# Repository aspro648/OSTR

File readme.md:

Open Source Turtle Robot (OSTR)
-------------------------------

I designed this project for a 10-hour workshop for [ChickTech.org](http://www.chicktech.org) whose goal is to introduce teenage women to STEM topics. The goals for this project were:

- Easy to build.
- Easy to program.
- Did something interesting.
- Low-cost so participants could take it home and continue to learn.

Robotics is the exciting intersection of a number of engineering fields including mechanical engineering, electrical engineering, and computer science. This project was designed to make learning about these fields accessible and exciting.

Turtle robots are controled by simple instructions like "forward(distance)" and "left(degrees)", and their visual tracks are instructive as well as entertaining. They also demonstrate how systems with simple rules can have complex behaviors, something we see in nature all the time.

New to Version 2 is the shift from the Adafruit [Trinket Pro](https://www.adafruit.com/product/2010) to their [ItsyBitsy 32U4 3V](https://www.adafruit.com/product/3675) which enables USB communication for easier troubleshooting, or the [ItsyBitsy M0 Express](https://www.adafruit.com/product/3727) which allows programing in Python!

Python is a popular and easy to learn programming language that already has Turle Graphics built in.  Since the robots instructions are the same, programs and paterns can be evaluated on the computer and then run on the robot. 
```python
from turtle import *

for x in range(5):
    forward(100)
    right(144)
```

Here is a great Hour of Code tutorial to get you introduced to Python Turtle: [https://groklearning.com/hoc/activity/snowflake/](https://groklearning.com/hoc/activity/snowflake/).  The only thing pysical Turtle Robot can't do is change colors automatically, but you can alway swap the pens around manually.

### Video of Turtle Robot (V1) in action:

This robot has been refined through a number workshops, but still has room for improvement.  Please share your ideas and modifications so it can continue to improve.

Bill Of Materials
-----------------
In bulk quantities, the cost per robot is about $40.  The Bill of Materials is available [here](/V2/BOM.md).
Having told you the at-cost and provided you my BOM, I'd still offer to [sell you a kit](https://www.tindie.com/products/MakersBox/open-source-turtle-robot-ostr/) if you'd like to pay for the convenience of a single-source or you don't have access to a 3D printer.  This also allows me continue development for future workshops.

Design Files
------------
The electronics were designed using Open Source [KiCad](http://kicad.org/). Design files are located in the [design_files](V2/design_files/) folder.  You can oogle the [schematic](V2/docs/Schematic.pdf).

The 3D Design files were created with a combination of [FreeCad](https://www.freecadweb.org/), [OpenSCAD](https://www.openscad.org/) (both Open Source), and online [TinkerCad](https://www.tinkercad.com/).  Design files and STLs are located in the [3D](V2/3D/) folder.

Firmware
--------
This project is programed using Open Source [Arduino](https://www.arduino.cc/) or Adafruit's [Circuit Python](https://learn.adafruit.com/welcome-to-circuitpython/what-is-circuitpython) depending on the microcontroller used. The firmware is located in the [firmware](V2/firmware/) folder.  Instructions for setting up the Arduino environment for the ItsyBitsy 32U4 are at [https://learn.adafruit.com/introducting-itsy-bitsy-32u4/](https://learn.adafruit.com/introducting-itsy-bitsy-32u4/).

Assembly Instructions
---------------------
[https://www.instructables.com/id/OSTR/](https://www.instructables.com/id/OSTR/).  
Also, check the [docs](V2/docs/) folder for handouts, etc.  May still have pictures of V1 assembly, but they are nearly identical.

License
-------
[Attribution-ShareAlike 3.0 United States (CC BY-SA 3.0 US)](https://creativecommons.org/licenses/by-sa/3.0/us/)

You are free to:

- Share — copy and redistribute the material in any medium or format
- Adapt — remix, transform, and build upon the material

Under the following terms:

- Attribution — You must give appropriate credit, provide a link to the license, and indicate if changes were made. You may do so in any reasonable manner, but not in any way that suggests the licensor endorses you or your use.
- ShareAlike — If you remix, transform, or build upon the material, you must distribute your contributions under the same license as the original.

Certified Open Source:
----------------------
This project as been certified by the [Open Source Hardward Association](https://certification.oshwa.org/):

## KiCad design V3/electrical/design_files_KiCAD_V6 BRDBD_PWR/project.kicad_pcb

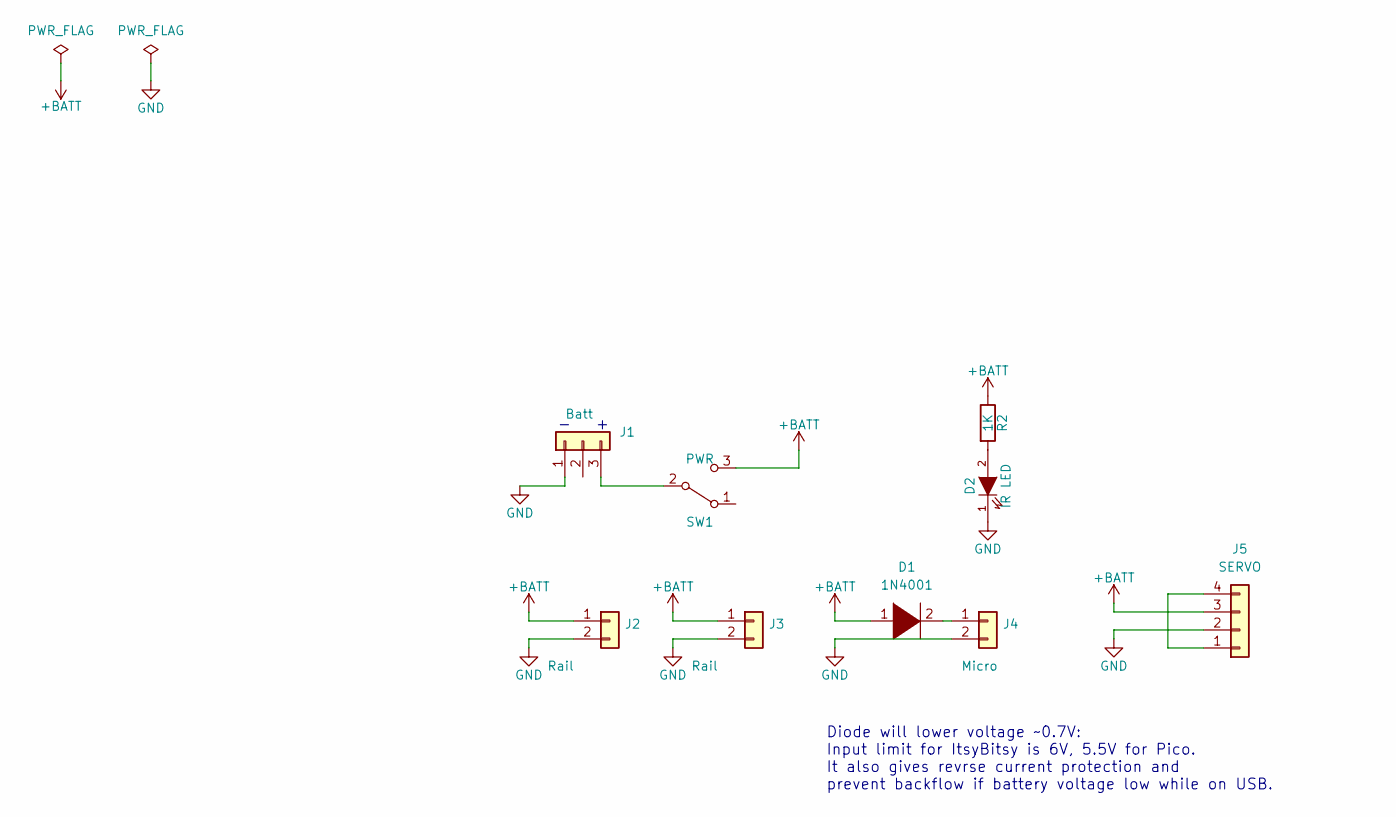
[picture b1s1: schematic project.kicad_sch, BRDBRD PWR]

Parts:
D1: 1N4001; D_DO-34_SOD68_P7.62mm_Horizontal
D2: IR LED; LED_D3.0mm
J1: Batt; TerminalBlock_Phoenix_PT-1,5-3-3.5-H_1x03_P3.50mm_Horizontal
J2, J3: Rail; PinHeader_1x02_P2.54mm_Vertical
J4: Micro; PinHeader_1x02_P2.54mm_Vertical
J5: SERVO; PinHeader_1x04_P2.54mm_Vertical
R2: 1K; Resistor_Horz
SW1: PWR; SW_Micro_SPST

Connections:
+BATT: D1.1 (K), J2.1, J3.1, J5.3, R2.1, SW1.3 (C)
GND: D2.1 (K), J1.1, J2.2, J3.2, J4.2, J5.2
unnamed: D2.2 (A), R2.2
unnamed: J1.3, SW1.2 (B)
unnamed: D1.2 (A), J4.1
unnamed: J5.1, J5.4

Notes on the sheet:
Diode will lower voltage ~0.7V: Input limit for ItsyBitsy is 6V, 5.5V for Pico. It also gives revrse current protection and prevent backflow if battery voltage low while on USB.
- +

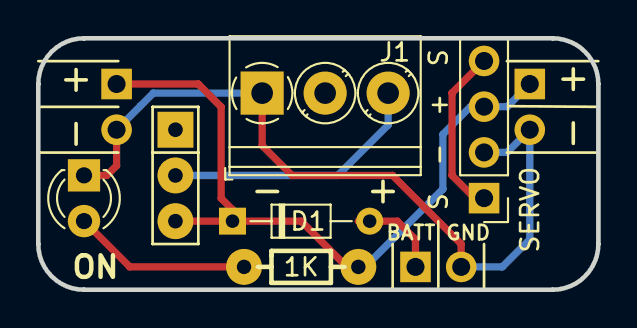
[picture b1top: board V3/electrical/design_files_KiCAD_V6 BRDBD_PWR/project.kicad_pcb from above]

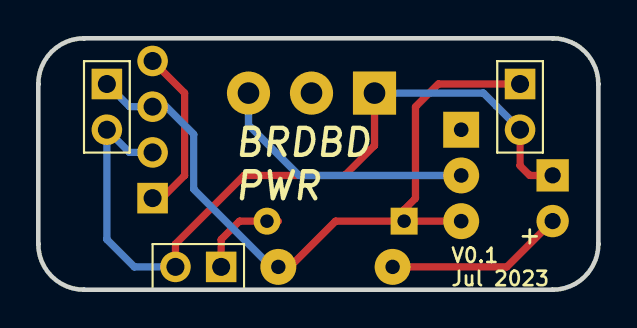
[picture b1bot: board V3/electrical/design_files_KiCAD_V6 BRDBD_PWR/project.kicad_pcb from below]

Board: 2 copper layers, 31.1 x 14.0 mm, 9 parts (3 on the bottom side), 6 nets.

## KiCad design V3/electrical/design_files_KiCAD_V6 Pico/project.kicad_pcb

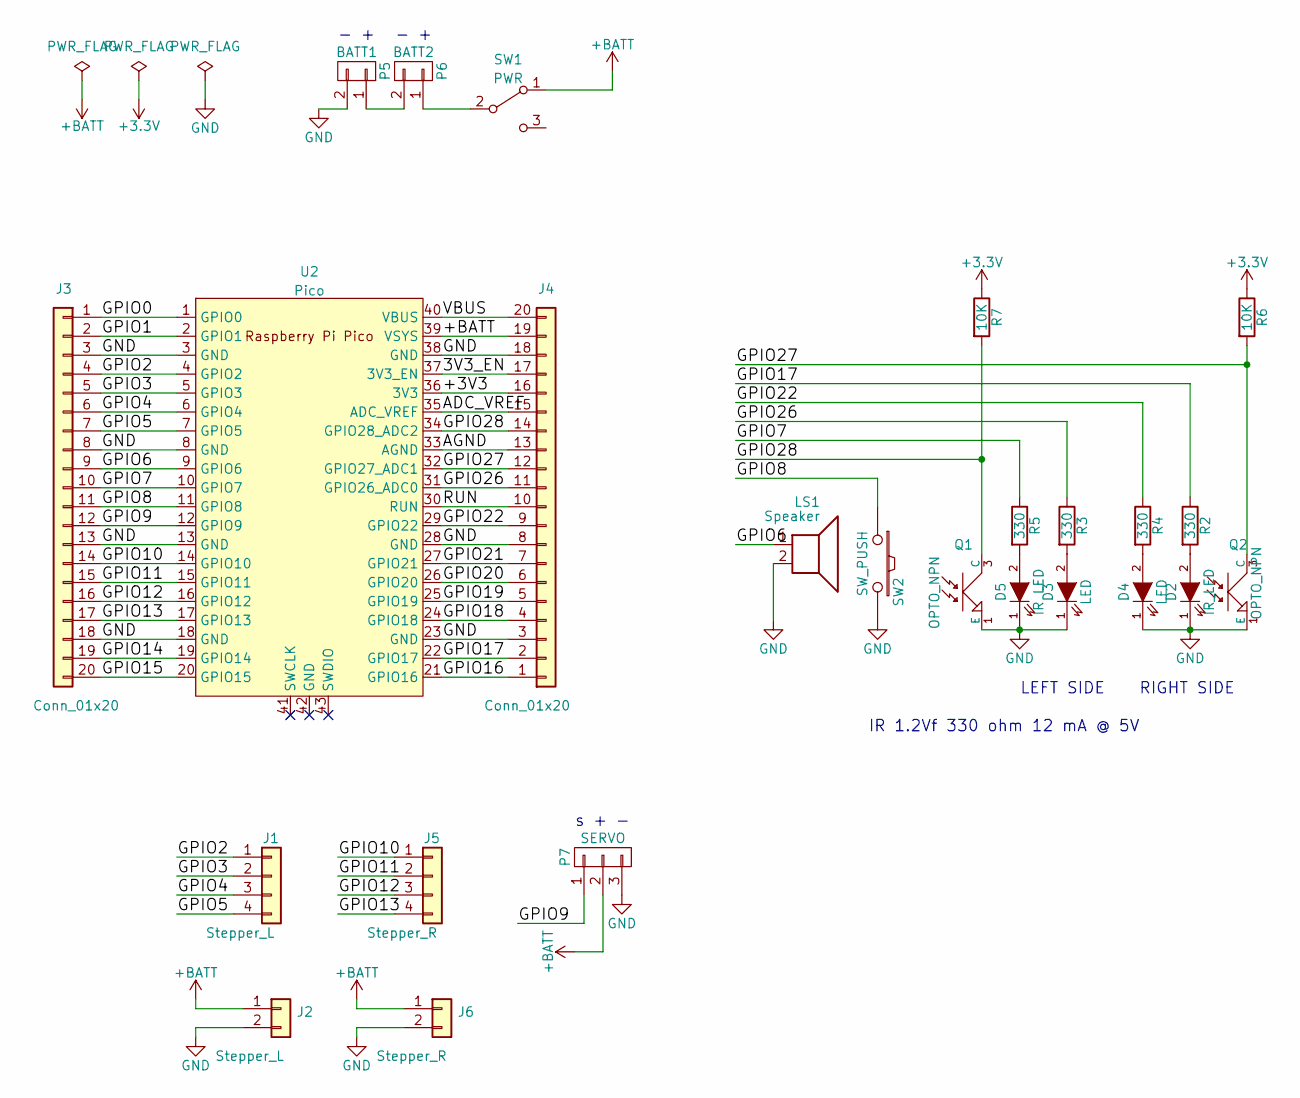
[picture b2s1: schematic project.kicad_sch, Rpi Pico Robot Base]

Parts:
D2: IR_LED; LED-3MM_RA
D3, D4: LED; LED-3MM_RA
D5: IR LED; LED-3MM_RA
J1: Stepper_L; PinHeader_1x04_P2.54mm_Vertical
J2: Stepper_L; PinHeader_1x02_P2.54mm_Vertical
J3, J4: Conn_01x20; PinHeader_1x20_P2.54mm_Vertical
J5: Stepper_R; PinHeader_1x04_P2.54mm_Vertical
J6: Stepper_R; PinHeader_1x02_P2.54mm_Vertical
LS1: Speaker; PS1240_piezo
P5: BATT1; TerminalBlock_Pheonix_PT-3.5mm_2pol
P6: BATT2; TerminalBlock_Pheonix_PT-3.5mm_2pol
P7: SERVO; Pin_Header_Straight_1x03
Q1, Q2: OPTO_NPN; PHOTOTRANS-RA
R2, R3, R4, R5: 330; Resistor_Horz
R6, R7: 10K; Resistor_Horz
SW1: PWR; SW_Micro_SPST
SW2: SW_PUSH; SW_PUSH_SMALL
U2: Pico; RPi_Pico_SMD_TH

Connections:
+BATT: J2.1, J4.19, J6.1, P7.2, SW1.1 (A), U2.39 (VSYS)
/3V3_EN: J4.17, U2.37 (3V3_EN)
/ADC_VREF: J4.15, U2.35 (ADC_VREF)
/AGND: J4.13, U2.33 (AGND)
/GPIO0: J3.1, U2.1 (GPIO0)
/GPIO1: J3.2, U2.2 (GPIO1)
/GPIO2: J1.1, J3.4, U2.4 (GPIO2)
/GPIO3: J1.2, J3.5, U2.5 (GPIO3)
/GPIO4: J1.3, J3.6, U2.6 (GPIO4)
/GPIO5: J1.4, J3.7, U2.7 (GPIO5)
/GPIO6: J3.9, LS1.1, U2.9 (GPIO6)
/GPIO7: J3.10, R5.1, U2.10 (GPIO7)
/GPIO8: J3.11, SW2.1, U2.11 (GPIO8)
/GPIO9: J3.12, P7.1, U2.12 (GPIO9)
/GPIO10: J3.14, J5.1, U2.14 (GPIO10)
/GPIO11: J3.15, J5.2, U2.15 (GPIO11)
/GPIO12: J3.16, J5.3, U2.16 (GPIO12)
/GPIO13: J3.17, J5.4, U2.17 (GPIO13)
/GPIO14: J3.19, U2.19 (GPIO14)
/GPIO15: J3.20, U2.20 (GPIO15)
/GPIO16: J4.1, U2.21 (GPIO16)
/GPIO17: J4.2, R2.1, U2.22 (GPIO17)
/GPIO18: J4.4, U2.24 (GPIO18)
/GPIO19: J4.5, U2.25 (GPIO19)
/GPIO20: J4.6, U2.26 (GPIO20)
/GPIO21: J4.7, U2.27 (GPIO21)
/GPIO22: J4.9, R4.1, U2.29 (GPIO22)
/GPIO26: J4.11, R3.1, U2.31 (GPIO26_ADC0)
/GPIO27: J4.12, Q2.3 (C), R6.2, U2.32 (GPIO27_ADC1)
/GPIO28: J4.14, Q1.3 (C), R7.2, U2.34 (GPIO28_ADC2)
/RUN: J4.10, U2.30 (RUN)
/VBUS: J4.20, U2.40 (VBUS)
GND: D2.1 (K), D3.1 (K), D4.1 (K), D5.1 (K), J2.2, J3.3, J3.8, J3.13, J3.18, J4.3, J4.8, J4.18, J6.2, LS1.2, P5.2, P7.3, Q1.1 (E), Q2.1 (E), SW2.2, U2.3 (GND), U2.8 (GND), U2.13 (GND), U2.18 (GND), U2.23 (GND), U2.28 (GND), U2.38 (GND)
unnamed: D2.2 (A), R2.2
unnamed: D3.2 (A), R3.2
unnamed: D4.2 (A), R4.2
unnamed: D5.2 (A), R5.2
unnamed: P5.1, P6.2
unnamed: P6.1, SW1.2 (B)

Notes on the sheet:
IR 1.2Vf 330 ohm 12 mA @ 5V
LEFT SIDE RIGHT SIDE
- +
s + -

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
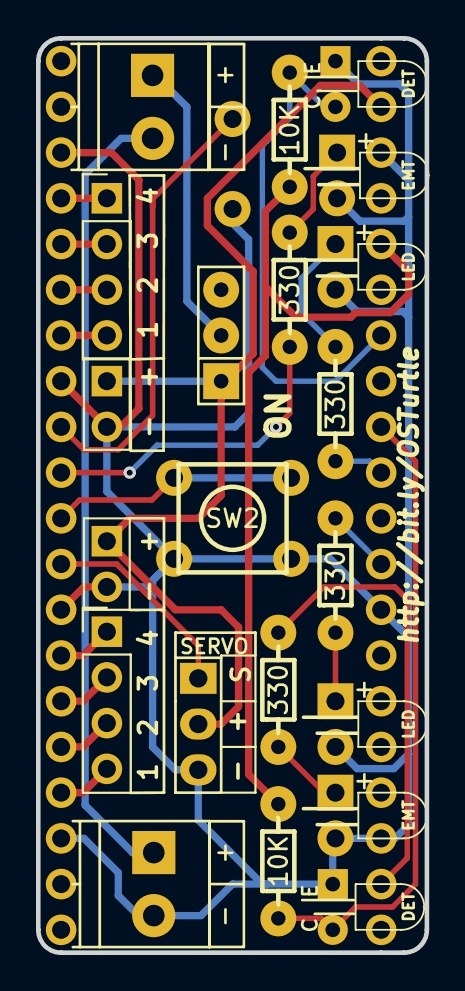
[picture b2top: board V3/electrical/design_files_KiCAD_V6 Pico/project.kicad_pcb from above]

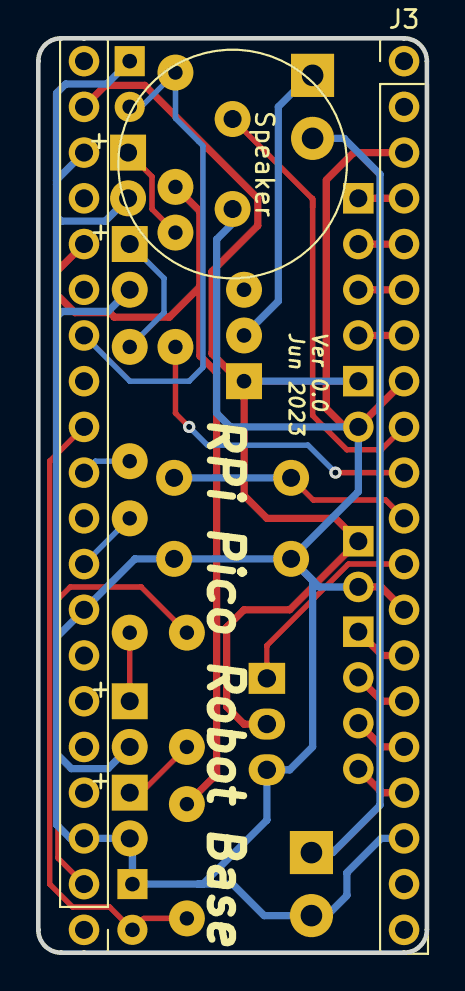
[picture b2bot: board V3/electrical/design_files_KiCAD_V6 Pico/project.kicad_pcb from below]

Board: 2 copper layers, 21.6 x 50.8 mm, 24 parts (3 on the bottom side), 26 nets.

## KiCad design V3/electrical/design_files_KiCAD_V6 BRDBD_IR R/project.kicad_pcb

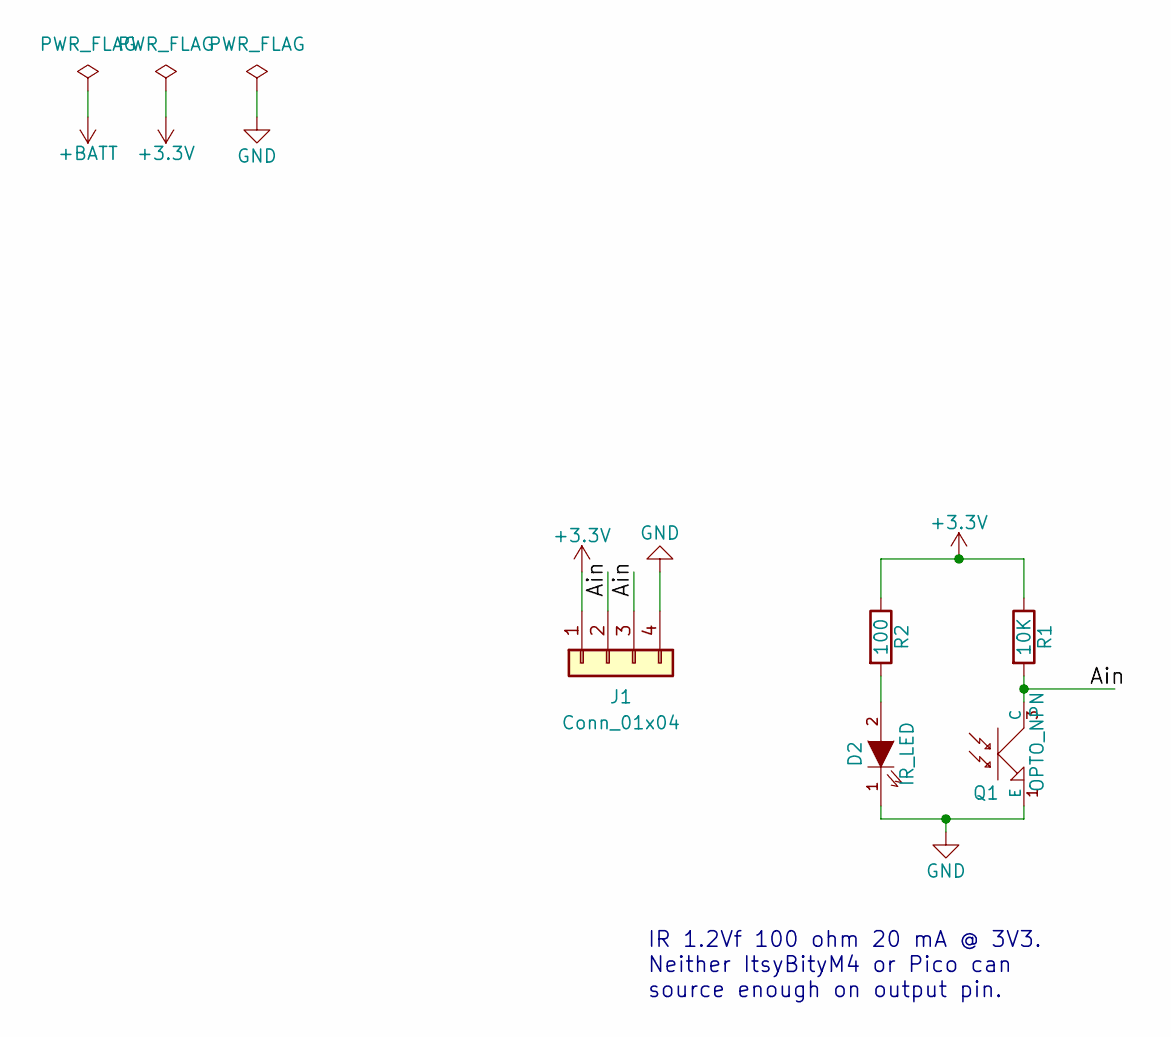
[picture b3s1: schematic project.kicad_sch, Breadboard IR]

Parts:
D2: IR_LED; LED-3MM_RA
J1: Conn_01x04; PinHeader_1x04_P2.54mm_Vertical
Q1: OPTO_NPN; PHOTOTRANS-RA
R1: 10K; Resistor_Horz
R2: 100; Resistor_Horz

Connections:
+3V3: J1.1, R1.1, R2.1
/Ain: J1.2, J1.3, Q1.3 (C), R1.2
GND: D2.1 (K), J1.4, Q1.1 (E)
unnamed: D2.2 (A), R2.2

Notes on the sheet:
IR 1.2Vf 100 ohm 20 mA @ 3V3. Neither ItsyBityM4 or Pico can source enough on output pin.

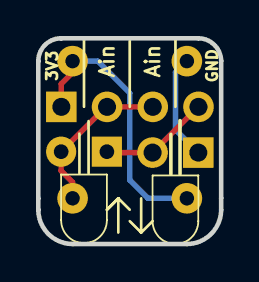
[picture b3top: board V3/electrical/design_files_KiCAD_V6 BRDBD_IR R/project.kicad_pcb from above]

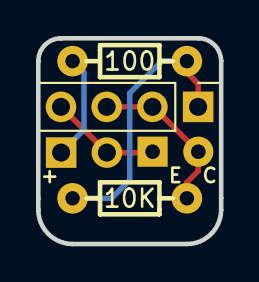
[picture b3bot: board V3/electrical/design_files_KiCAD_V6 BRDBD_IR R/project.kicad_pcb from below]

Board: 2 copper layers, 10.2 x 11.4 mm, 5 parts (3 on the bottom side), 4 nets.

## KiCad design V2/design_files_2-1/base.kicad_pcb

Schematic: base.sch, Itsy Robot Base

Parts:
C1: 100uF; C_Radial_D7.5_L11.2_P2.5
C2: 10uF; C_Radial_D5_L11_P2.5
C3: 1uF; C_Disc_D3_P2.5
D2: IR_LED; LED-3MM_RA
D3, D4: LED; LED-3MM
D5: IR LED; LED-3MM_RA
J1: Isty_Left; Pin_Header_Straight_1x14_Pitch2.54mm
J2: Itsy_right; Pin_Header_Straight_1x14_Pitch2.54mm
LS1: Speaker; PS1240_piezo
P3: LEFT_STEPPER; JST_B5B-XH-A
P4: RIGHT_STEPPER; JST_B5B-XH-A
P5: BATT1; TerminalBlock_Pheonix_PT-3.5mm_2pol
P6: BATT2; TerminalBlock_Pheonix_PT-3.5mm_2pol
P7: SERVO; Pin_Header_Straight_1x03
Q1, Q2: OPTO_NPN; PHOTOTRANS-RA
R2, R3, R4, R5: 330; Resistor_Horz
R6, R7: 10K; Resistor_Horz
SW1: SPST; SW_Micro_SPST
SW2: SW_PUSH; SW_PUSH_SMALL
U1: ULN2803; DIP-18_W7.62mm

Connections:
+3V3: J1.2, R6.1, R7.1
/A0: J1.5, LS1.1
/A1: J1.6, P7.1
/A2: J1.7, Q2.3 (C), R6.2
/A3: J1.8, Q1.3 (C), R7.2
/A4: J1.9, U1.3 (3B)
/A5: J1.10, U1.4 (4B)
/BAT: C1.1, C2.1, C3.1, J2.1, P3.5, P4.5, P7.2, SW1.2, U1.10 (COM)
/D5: J2.10, R2.1, R5.1
/D7: J2.9, R3.1
/D9: J2.8, U1.8 (8B)
/D10: J2.7, U1.2 (2B)
/D11: J2.6, R4.1
/D12: J2.5, SW2.1
/D13: J2.4, U1.1 (1B)
/D14: J1.13, U1.7 (7B)
/D15: J1.11, U1.5 (5B)
/D16: J1.12, U1.6 (6B)
/RST: J1.1
/RX: J2.14
/SCL: J2.11
/SDA: J2.12
/TX: J2.13
/USB: J2.3
GND: C1.2, C2.2, C3.2, D2.1 (K), D3.1 (K), D4.1 (K), D5.1 (K), J2.2, LS1.2, P5.1, P7.3, Q1.1 (E), Q2.1 (E), SW2.2, U1.9 (GND)
unnamed: D2.2 (A), R2.2
unnamed: D3.2 (A), R3.2
unnamed: D4.2 (A), R4.2
unnamed: D5.2 (A), R5.2
unnamed: P3.1, U1.18 (1C)
unnamed: P3.2, U1.17 (2C)
unnamed: P3.3, U1.16 (3C)
unnamed: P3.4, U1.15 (4C)
unnamed: P4.1, U1.14 (5C)
unnamed: P4.2, U1.13 (6C)
unnamed: P4.3, U1.12 (7C)
unnamed: P4.4, U1.11 (8C)
unnamed: P5.2, P6.1
unnamed: P6.2, SW1.1

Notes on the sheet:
https://www.digikey.com/short/qcrr5m B5B-XH-A
USB
- +
s + -
LEFT SIDE RIGHT SIDE
IR 1.2Vf 330 ohm 12 mA @ 5V

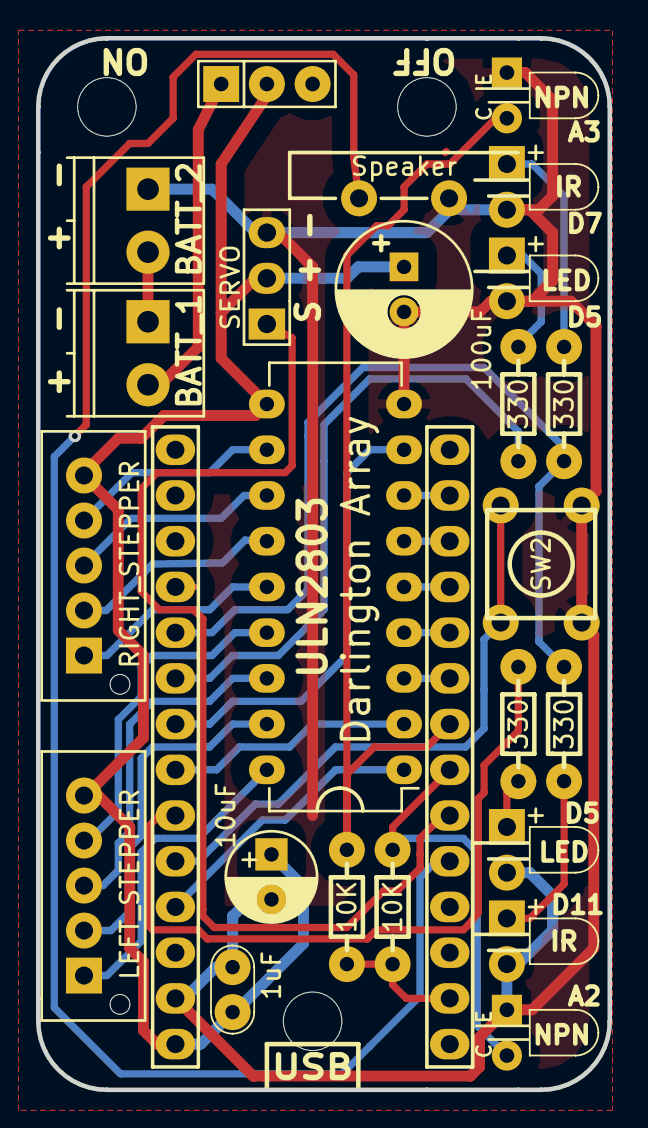
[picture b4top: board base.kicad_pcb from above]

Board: 2 copper layers, 31.8 x 58.4 mm, 31 parts (0 on the bottom side), 33 nets.

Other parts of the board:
P9, P9#2, P9#3: CONN_01X01; Lego_Pad
VAL: MadeInOregonRev25
VAL#2: MB225rev

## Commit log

2018-04-18 Update PCB link and BOM
2018-04-22 Updated photo
2018-04-22 Updated BOM, labels
2018-04-27 Updated nameplate & chassis
2018-05-25 Updated firmware and mechanicals
2018-06-16 Font Updates
2018-10-23 Updted BOM
2018-10-26 Updating Read.me. Not a big fan of markdown.
2019-09-10 makecode first try
2019-09-11 Removing makecode
2019-11-18 Firmware and BOM updates
2019-11-27 Merge branch 'master' of https://github.com/aspro648/OSTR
    # Conflicts:
    # V2/firmware/CircuitPython M4/turtle_wheel_calibration.py
2020-02-16 Workshop prep
2020-02-17 V2.2 pannel for fab
2020-02-18 Firmware updates
2020-02-19 Finalized firmware for workshop
2020-03-03 Firmware zip file
2020-10-23 Updating BOM
2021-05-25 Documentatoin
2021-11-08 Update readme.md
    https://forum.kicad.info/t/warning-avoid-all-links-to-kicad-pcb-org-use-kicad-org/31521
2023-07-17 V3 Updates
2023-08-16 Cleanup
